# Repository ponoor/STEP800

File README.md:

# STEP800
8-axis stepper motor driver for Open Sound Control

STEP800 is a 8-axis stepper motor driver designed for art or design projects. STEP800 combines the following elements into one single board:

- [Arduino Zero](https://www.arduino.cc/en/Guide/ArduinoZero)
- Ethernet shield
- 8 stepper motor drivers
- Sensor inputs for homing

The current firmware is focused on working with [Open Sound Control](http://opensoundcontrol.org/) (OSC) via Ethernet, which is a common protocol for creative coding environments, like openFrameworks, Processing, Max, Unity, or Touch Designer.

Stepper driver chips are STMicroelectronics's [L6470](https://www.st.com/en/motor-drivers/l6470.html) which provide most of functionalities as a stepper driver.

Friend of STEP800 : [STEP400](https://github.com/ponoor/STEP400)

## Store
https://ponoor.com/en/shop/

## Documentation
https://ponoor.com/en/docs/step-series/

Forum: https://github.com/ponoor/step-series-support/discussions

## Repository Contents
### Firmware

**Important Note:**
The latest firmware is available at [STEP-series Universal Firmware](https://github.com/ponoor/step-series-universal-firmware) repository. Following directories and Releases are not maintained anymore. 

These 2 folders contain same codes.
- [/STEP800_firmware](https://github.com/ponoor/STEP800/tree/main/STEP800_firmware) : Arduino Sketch folder
- [/firmware-platformIO/STEP800_firmware](https://github.com/ponoor/STEP800/tree/main/firmware-platformIO/STEP800_firmware) : PlatformIO folder

### Hardware
[/hardware](https://github.com/ponoor/STEP800/tree/main/hardware) : Eagle design files, BOM lists, and a schematics PDF

### Others
[/configTool](https://github.com/ponoor/STEP800/tree/main/configTool) : The configuration tool consists of a html and JavaScritpts.

## Firmware dependency
- **[OSC Library](https://github.com/CNMAT/OSC)** from CNMAT
- **[Ponoor L6470 Library](https://github.com/ponoor/Ponoor_L6470_Library)**
- **[ArduinoJSON Library](https://arduinojson.org/)**
- **[Adafruit SleepyDog Arduino Library](https://github.com/adafruit/Adafruit_SleepyDog)**

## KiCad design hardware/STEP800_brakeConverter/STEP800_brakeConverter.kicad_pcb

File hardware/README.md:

# Diagram
```mermaid
flowchart LR
	MCU ---|SPI/SERCOM4| W5500 --- Ethernet
	MCU --- |SPI/SERCOM3|L6470 --> Motor
  MCU --> |SPI/SERCOM2|74HC165 --> 74HC595 --> MCU
	HomeSw -->|SW| L6470
	DIPSW --> 74HC165
	74HC595 --> Brake
  ```
  
  Check the [document](https://ponoor.com/en/docs/step-series/technical-information/hardware-step800/) for details.

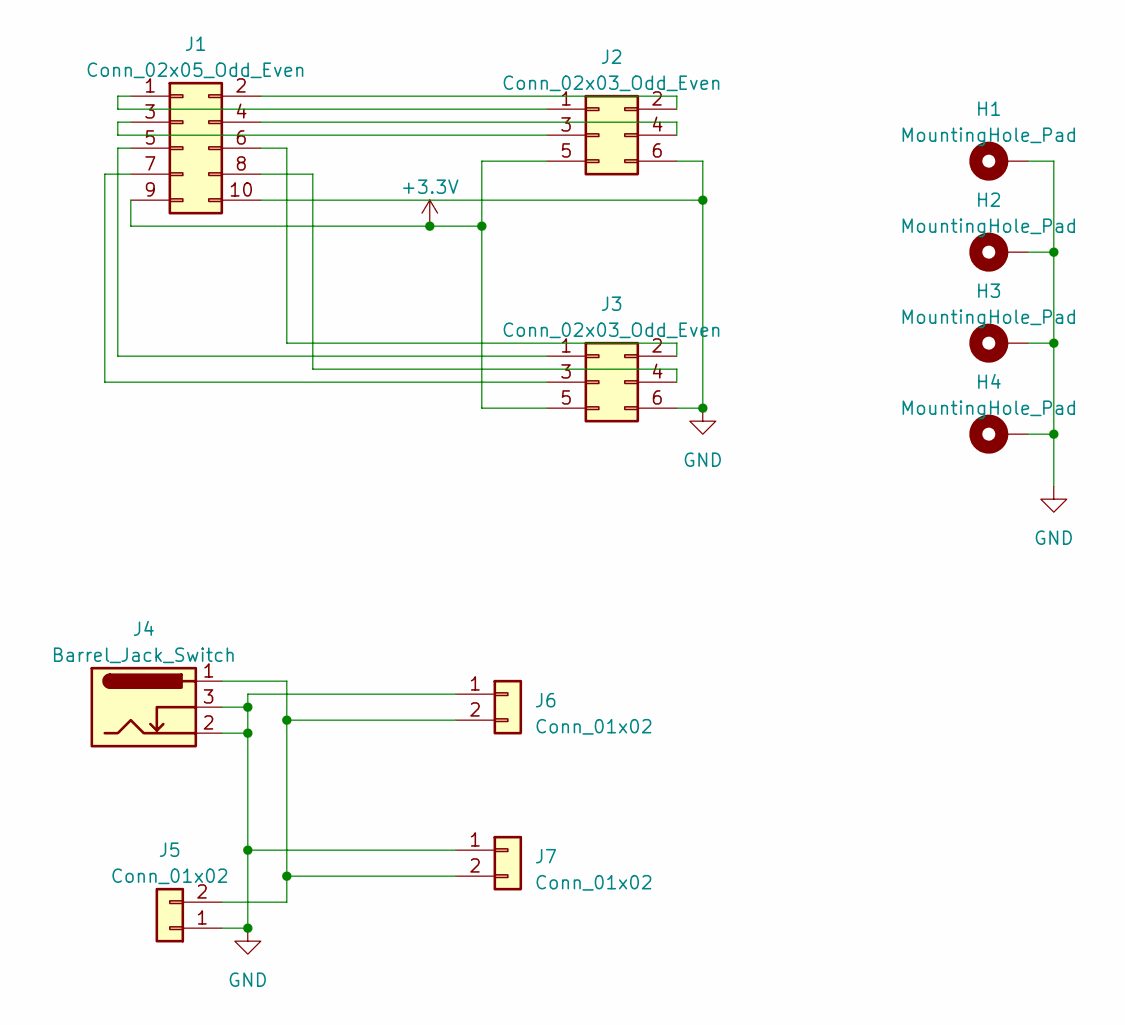
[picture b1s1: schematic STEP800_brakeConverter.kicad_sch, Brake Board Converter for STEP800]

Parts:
H1, H2, H3, H4: MountingHole_Pad; MountingHole_3.2mm_M3_Pad_TopBottom
J1: Conn_02x05_Odd_Even; IDC-Header_2x05_P2.54mm_Vertical
J2, J3: Conn_02x03_Odd_Even; IDC-Header_2x03_P2.54mm_Vertical
J4: Barrel_Jack_Switch; BarrelJack_GCT_DCJ200-10-A_Horizontal
J5, J6, J7: Conn_01x02; PhoenixContact_MCV_1,5_2-G-3.81_1x02_P3.81mm_Vertical

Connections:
+3.3V: J1.9, J2.5, J3.5
GND: H1.1, H2.1, H3.1, H4.1, J1.10, J2.6, J3.6, J4.2, J4.3, J5.1, J6.1, J7.1
unnamed: J1.1, J2.1
unnamed: J1.2, J2.2
unnamed: J1.3, J2.3
unnamed: J1.4, J2.4
unnamed: J1.5, J3.1
unnamed: J1.6, J3.2
unnamed: J1.7, J3.3
unnamed: J1.8, J3.4
unnamed: J4.1, J5.2, J6.2, J7.2

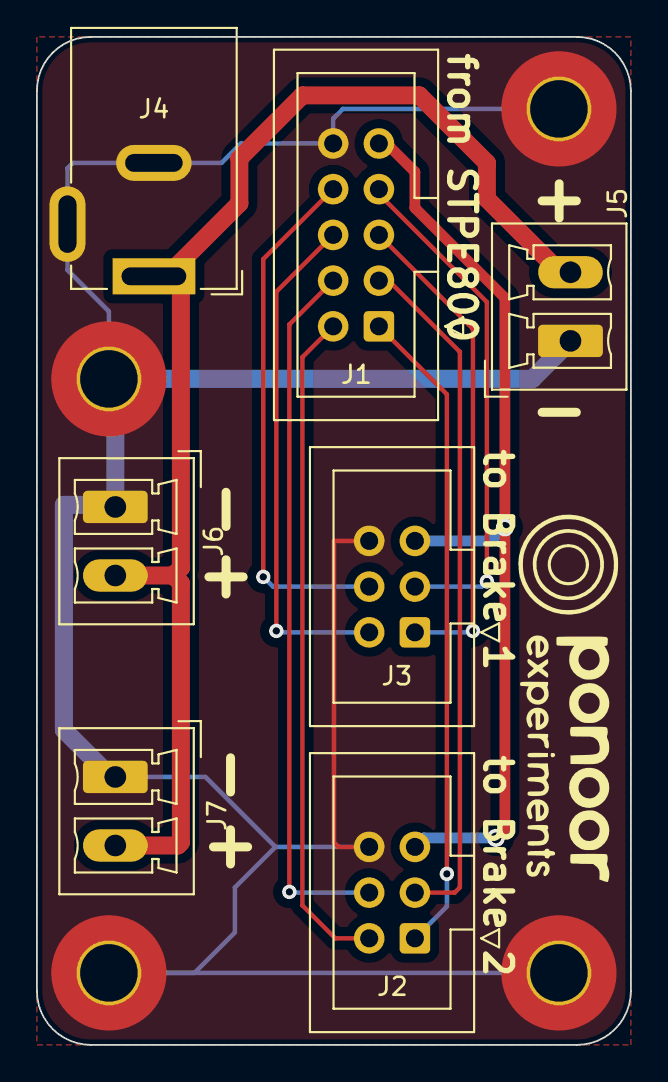
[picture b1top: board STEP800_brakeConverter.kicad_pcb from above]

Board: 2 copper layers, 33.0 x 56.0 mm, 11 parts (0 on the bottom side), 11 nets.

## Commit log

2021-04-14 Added hardware design files
2021-04-20 Added firmware files
2021-04-23 Added multiple boards support
2021-04-27 Fixed a SPI pin for shift registers
2021-04-28 Fixed loading myIp, outPort and mac when the DIP sw changed.
    And PROTOTYPE_BLACK bugs fix
2021-04-28 Updated the diagnosis outputs
2021-04-28 Updated hardware design files
2021-04-30 Fixed the L6470 reset pin logic state for prototype pcb
2021-05-03 Fixed the wrong parsing when loading integer as bool in the config.txt
2021-05-07 Silk adjustments for the Eagle board design file
2021-05-09 Added the hardware inspection sketch
2021-05-10 Updated the hardware test sketch
2021-05-17 Correct the external OSC frequency for prototype_black
2021-07-12 Rename test_prcedure.md to 1_preparation.md
2021-07-16 update the hardware test sketch
2021-08-30 configTools item name typo fixed
    goUntilTimeout
2021-08-30 configTool html+js update
2021-08-31 changed the directory name for the firmware
2021-09-01 changed a structure of directories
2021-09-03 Fixed the diagnosis tool serial output problem
2021-09-03 added hardware dimension files
2021-09-03 Fixed a usb serial output problem of the diagnosis tool
2021-09-05 config tool css+html update
2021-09-08 configTools CSS
2021-09-13 led test sketch
2021-09-14 led test sketch update
2021-10-18 Added configProductApplicable
2021-10-18 Update Arduino sketch folder
2021-11-25 Added minSpeed commands for the firmware and the config tool.
2021-11-25 added getMinSpeed command
2021-12-02 added /resetDeive and remove /resetDev
2021-12-08 added position report commands, update setElPos arguments
2021-12-08 updated Arduino sketch folder
2022-01-14 fixed `/getLowSpeedOptimizeThreshold` response bug.
2022-01-19 Fixed the thermal status return value
2022-02-13 check the homing status for motion/stop commands
2022-02-14 only `/run` can interrupt a homing among motion commands
    Other motion commands will be ignored during a homing.
2022-03-03 Fixed the incorrect `/getHomeSw` response.
2022-03-24 added the link to the latest firmware
2023-03-10 generate the brake board schematic
2023-03-10 generate the board layout
2023-03-17 brake board pcb design update
2023-04-05 brake conv gerber data for the prototype
2023-09-09 hardware test sketch update to adapt new SAMD SPI function name
2023-09-10 The hardware test sketch updated
    Added LED tests.
2024-03-03 typo
